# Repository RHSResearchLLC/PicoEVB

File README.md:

# PicoEVB: M.2/NGFF based Xilinx Artix-7 development board

PicoEVB is an affordable development board which can be used to evaluate and prototype 
PCI express designs using Xilinx Artix 7 FPGA on Windows or Linux hosts.
The board is designed around the Artix 7 (XC7A50T).

PicoEVB is a complete development system in a M.2 (NGFF) 2230 footprint. The JTAG cable
and all necessary power supplies are built in. It will work in the following slots:
 
- M.2 2230 Key A
- M.2 2230 Key E
- M.2 2280 Key M via an adapter [like this one](https://www.amazon.com/gp/product/B079NB8J3B)
- Full length mini PCIe via an adapter [like this one](https://www.amazon.com/dp/B01MR76H5F)
- PCIe x1, x4, x8, or x16 slot via an adapter [like this one](https://www.amazon.com/dp/B013U4401W) 

## Features
- PCI Express connection to the host via M.2 edge slot
- Built-in JTAG cable works with Vivado and Labtools
- Analog and digital IO

## Specifications

| Feature | Specification |
| --- | --- |
| FPGA | Xilinx Artix XC7A50T-2CSG325C |
| Form Factor | M.2 (NGFF), keyed for A and E slots |
| Dimensions | 22x30x3.8 mm |
| Host Interface | PCIe x1 gen 2 (5 Gb/s) |
| Host Tools | Vivado 2017.3 preferred |
| MGT Loopback | Yes |
| Built-in JTAG | Yes |
| External I/O configurations <BR/> via I/O connector | (digital+ differential analog) <BR/> 4+0 <BR/> 2+1 <BR/> 0+2 |
| External I/O via PCIe connector | 4x 3.3V digital I/O (configurable) |
| External MGT connection | 1x MGT via U.FL connectors |
| External clock ref | 1x clkin via U.FL connectors |
| User-controllable LEDs | 3 |

## Block Diagram

## How to get one

- [Product Website](https://www.picoevb.com)
- [Amazon](https://www.amazon.com/dp/B0779PC8S4)
- [Crowd Supply](https://www.crowdsupply.com/rhs-research/nanoevb)
- [EBay](https://www.ebay.com/itm/232775706324)

## More information

- [Check out the wiki](https://github.com/RHSResearchLLC/NanoEVB-X1/wiki)
- [Product Website](https://www.picoevb.com)

or contact info@nanoevb.com

** Note: This page applies to PicoEVB Rev D. For previous revs, select the rev from tags **

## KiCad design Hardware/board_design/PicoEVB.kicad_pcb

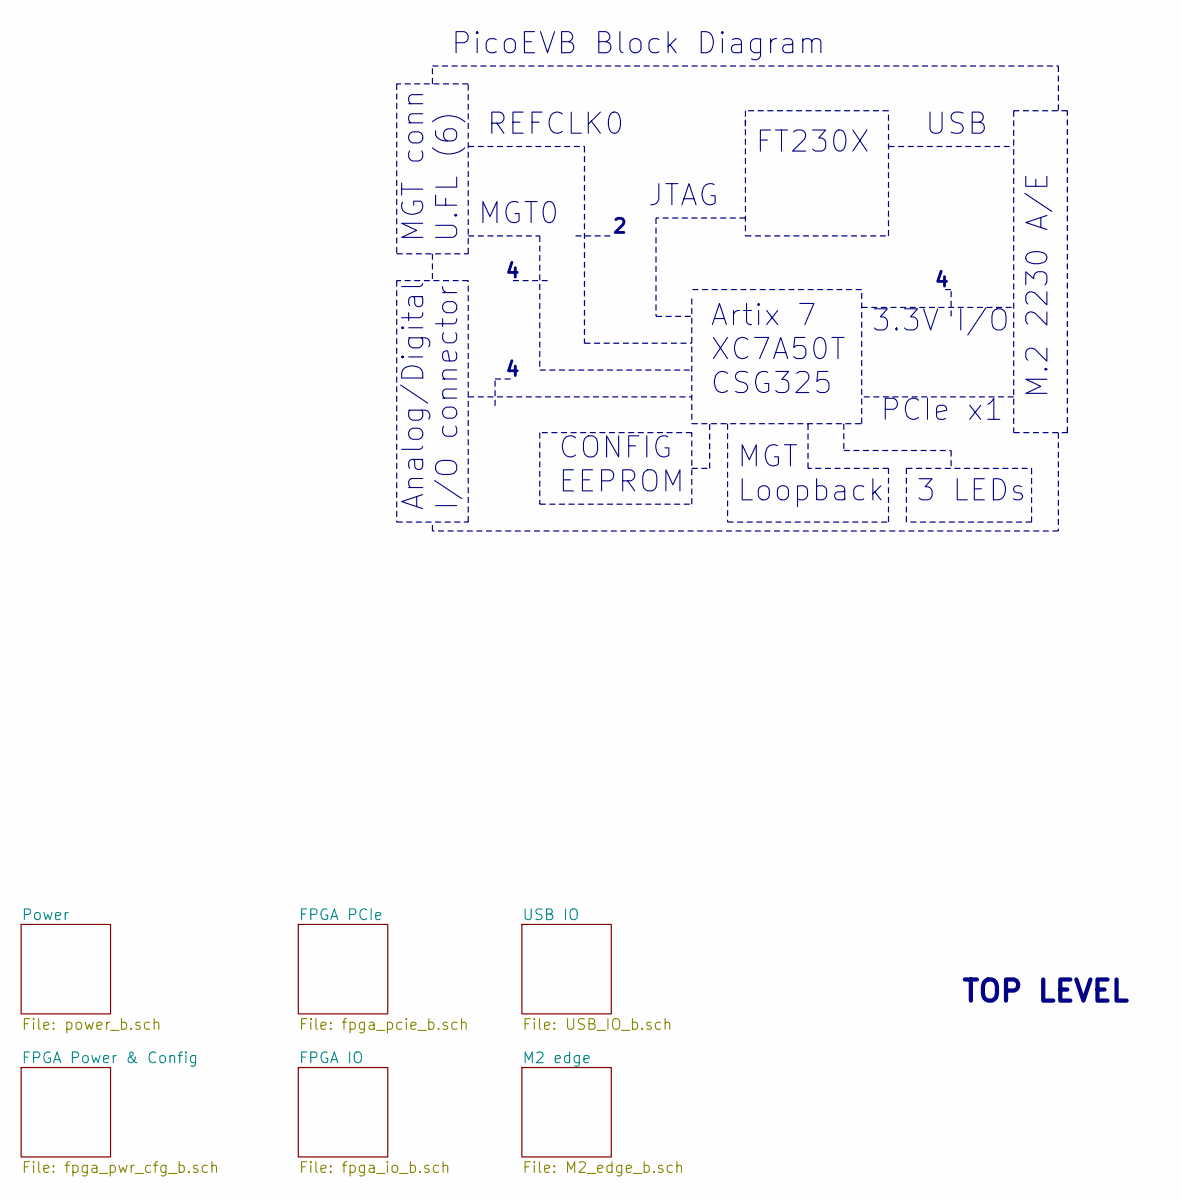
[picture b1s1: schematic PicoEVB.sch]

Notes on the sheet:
TOP LEVEL
M.2 2230 A/E
FT230X
USB
Artix 7 XC7A50T CSG325
PCIe x1
JTAG
MGT Loopback
Analog/Digital I/O connector
PicoEVB Block Diagram
3 LEDs
CONFIG EEPROM
MGT conn U.FL (6)
MGT0
REFCLK0
3.3V I/O

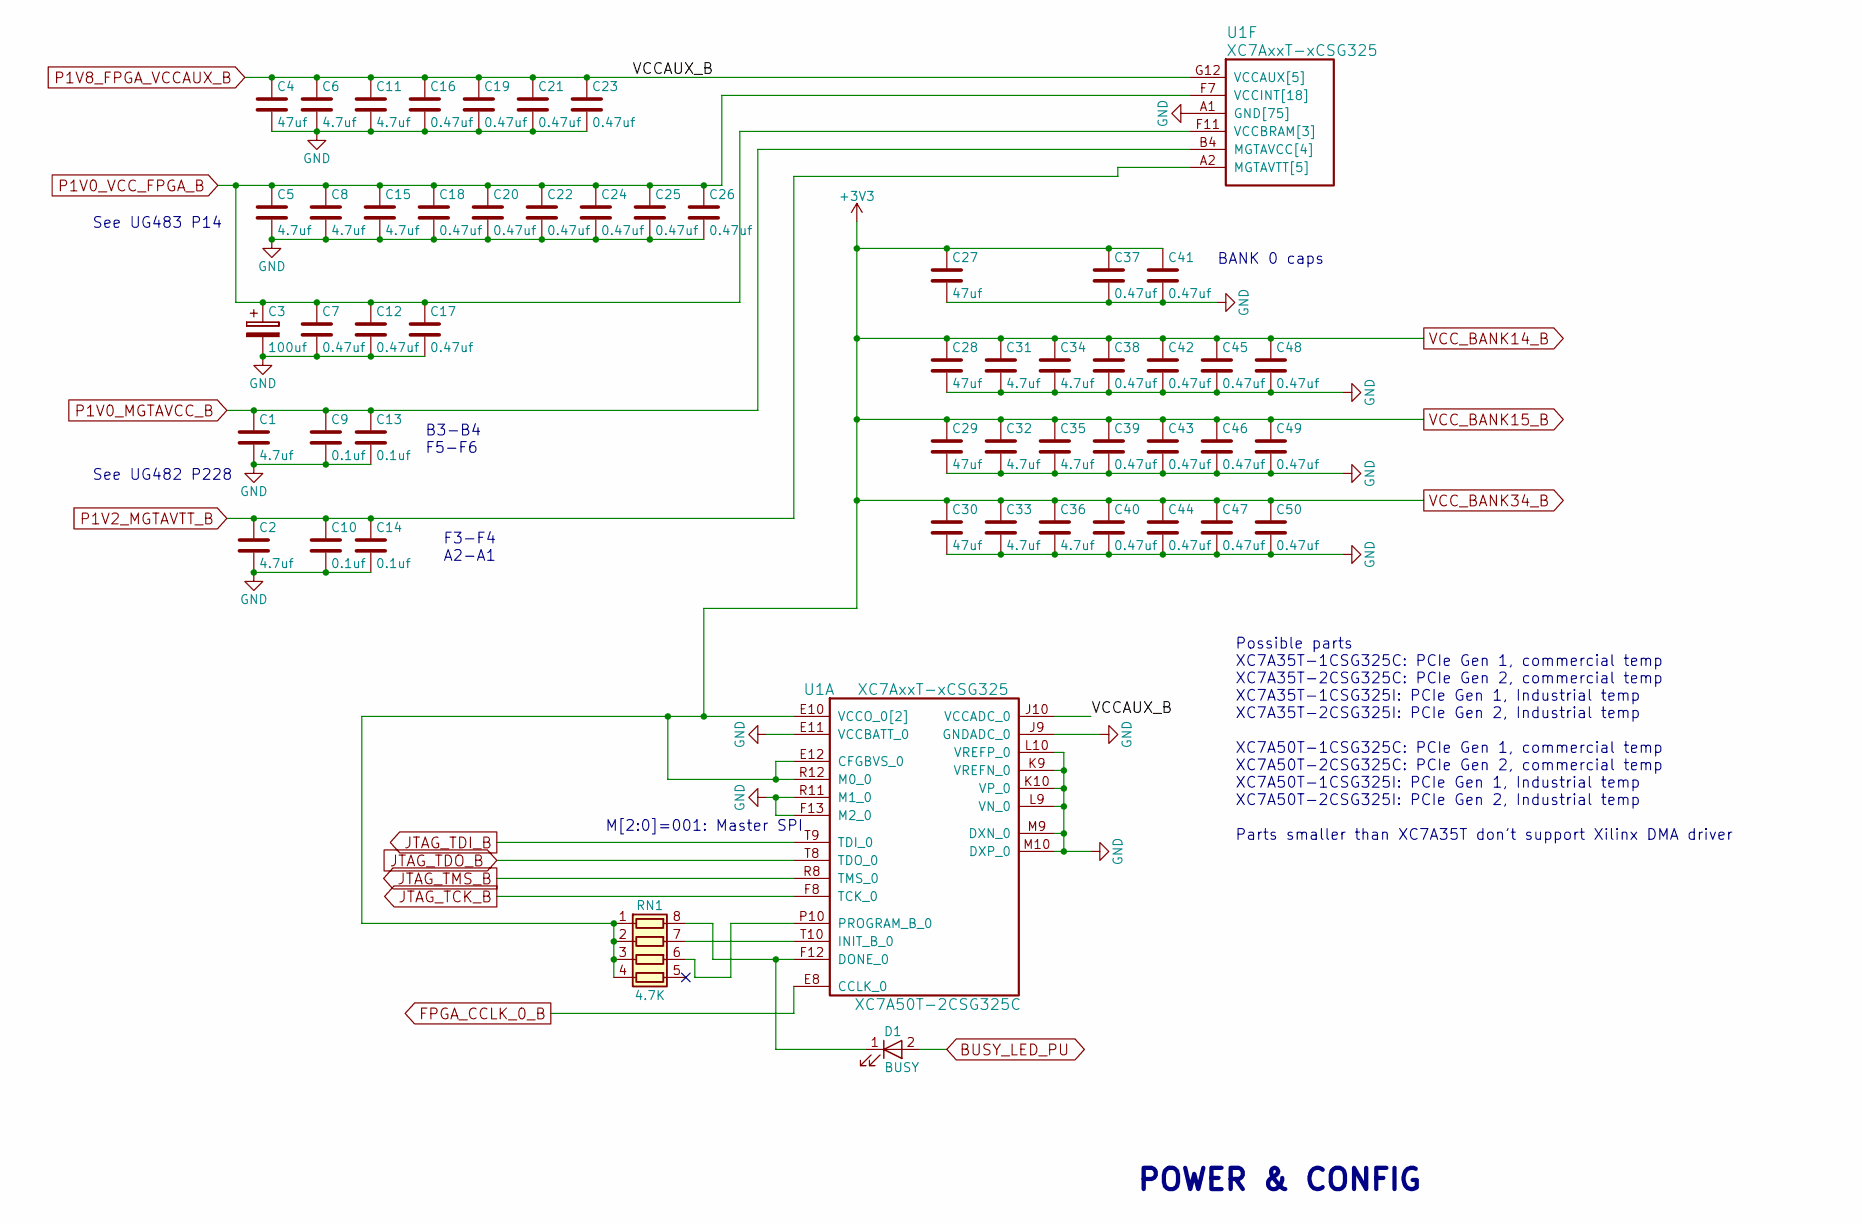
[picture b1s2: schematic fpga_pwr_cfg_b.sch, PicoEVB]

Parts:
C1, C2, C5, C6, C8, C11, C15, C31, C32, C33, C34, C35, C36: 4.7uf; c_0402; MPN CC0402MRX5R5BB475
C3: 100uf; C_0805; MPN F950J107MPAAQ2
C4, C27, C28, C29, C30: 47uf; C_0603; MPN GRM188R60G476ME15D
C7, C12, C16, C17, C18, C19, C20, C21, C22, C23, C24, C25, C26, C37, C38, C39, C40, C41, C42, C43, C44, C45, C46, C47, C48, C49, C50: 0.47uf; c_0201_least; MPN cc0201krx5r5bb474
C9, C10, C13, C14: 0.1uf; c_0201_least; MPN cc0201krx5r5bb104
D1: BUSY; LED_0402; MPN LNJ247W82RA
RN1: 4.7K; R_Array_Convex_4x0402; MPN 741X083472JP
U1: XC7AxxT-xCSG325

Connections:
BUSY_LED_PU: D1.2 (A); also elsewhere on the board
FPGA_CCLK_0_B: U1.E8 (CCLK_0); also elsewhere on the board
GND: C1.2, C2.2, C3.2, C4.2, C5.2, C6.2, C7.2, C8.2, C9.2, C10.2, C11.2, C12.2, C13.2, C14.2, C15.2, C16.2, C17.2, C18.2, C19.2, C20.2, C21.2, C22.2, C23.2, C24.2, C25.2, C26.2, C27.2, C28.2, C29.2, C30.2, C31.2, C32.2, C33.2, C34.2, C35.2, C36.2, C37.2, C38.2, C39.2, C40.2, C41.2, C42.2, C43.2, C44.2, C45.2, C46.2, C47.2, C48.2, C49.2, C50.2, U1.A1 (GND[75]), U1.A5 (GND[75]), U1.A7 (GND[75]), U1.A8 (GND[75]), U1.A11 (GND[75]), U1.A18 (GND[75]), U1.B3 (GND[75]), U1.B7 (GND[75]), U1.B8 (GND[75]), U1.B18 (GND[75]), U1.C2 (GND[75]), U1.C6 (GND[75]), U1.C7 (GND[75]), U1.C15 (GND[75]), U1.D3 (GND[75]), U1.D4 (GND[75]), U1.D7 (GND[75]), U1.D12 (GND[75]), U1.E2 (GND[75]), U1.E6 (GND[75]), U1.E7 (GND[75]), U1.E9 (GND[75]), U1.E11 (VCCBATT_0), U1.F4 (GND[75]), U1.F6 (GND[75]), U1.F10 (GND[75]), U1.F13 (M2_0), U1.F16 (GND[75]), U1.G1 (GND[75]), U1.G5 (GND[75]), U1.G6 (GND[75]), U1.G7 (GND[75]), U1.G9 (GND[75]), U1.G11 (GND[75]), U1.G13 (GND[75]), U1.H3 (GND[75]), U1.H4 (GND[75]), U1.H5 (GND[75]), U1.H6 (GND[75]), U1.H8 (GND[75]), U1.H10 (GND[75]), U1.H12 (GND[75]), U1.J1 (GND[75]), U1.J2 (GND[75]), U1.J3 (GND[75]), U1.J7 (GND[75]), U1.J9 (GNDADC_0), U1.J11 (GND[75]), U1.J13 (GND[75]), U1.J17 (GND[75]), U1.K4 (GND[75]), U1.K8 (GND[75]), U1.K9 (VREFN_0), U1.K10 (VP_0), U1.K12 (GND[75]), U1.K14 (GND[75]), U1.L1 (GND[75]), U1.L7 (GND[75]), U1.L9 (VN_0), U1.L10 (VREFP_0), U1.L11 (GND[75]), U1.L13 (GND[75]), U1.M8 (GND[75]), U1.M9 (DXN_0), U1.M10 (DXP_0), U1.M12 (GND[75]), U1.M18 (GND[75]), U1.N5 (GND[75]), U1.N7 (GND[75]), U1.N9 (GND[75]), U1.N11 (GND[75]), U1.N13 (GND[75]), U1.N15 (GND[75]), U1.P2 (GND[75]), U1.P8 (GND[75]), U1.P12 (GND[75]), U1.R9 (GND[75]), U1.R11 (M1_0), U1.T6 (GND[75]), U1.T16 (GND[75]), U1.U3 (GND[75]), U1.U13 (GND[75]), U1.V1 (GND[75]), U1.V10 (GND[75]), U1.V18 (GND[75]); also elsewhere on the board
JTAG_TCK_B: U1.F8 (TCK_0); also elsewhere on the board
JTAG_TDI_B: U1.T9 (TDI_0); also elsewhere on the board
JTAG_TDO_B: U1.T8 (TDO_0); also elsewhere on the board
JTAG_TMS_B: U1.R8 (TMS_0); also elsewhere on the board
unnamed: D1.1 (K), RN1.8 (R1.2), U1.F12 (DONE_0)
unnamed: RN1.6 (R3.2), U1.P10 (PROGRAM_B_0)
unnamed: RN1.7 (R2.2), U1.T10 (INIT_B_0)
P1V0_MGTAVCC_B: C1.1, C9.1, C13.1, U1.B4 (MGTAVCC[4]), U1.C5 (MGTAVCC[4]), U1.E5 (MGTAVCC[4]), U1.F5 (MGTAVCC[4]); also elsewhere on the board
P1V0_VCC_FPGA_B: C3.1, C5.1, C7.1, C8.1, C12.1, C15.1, C17.1, C18.1, C20.1, C22.1, C24.1, C25.1, C26.1, U1.F7 (VCCINT[18]), U1.F9 (VCCINT[18]), U1.F11 (VCCBRAM[3]), U1.G8 (VCCINT[18]), U1.G10 (VCCBRAM[3]), U1.H7 (VCCINT[18]), U1.H9 (VCCINT[18]), U1.H11 (VCCBRAM[3]), U1.J8 (VCCINT[18]), U1.J12 (VCCINT[18]), U1.K7 (VCCINT[18]), U1.K11 (VCCINT[18]), U1.L8 (VCCINT[18]), U1.L12 (VCCINT[18]), U1.M7 (VCCINT[18]), U1.M11 (VCCINT[18]), U1.N8 (VCCINT[18]), U1.N10 (VCCINT[18]), U1.N12 (VCCINT[18]), U1.P9 (VCCINT[18]), U1.P11 (VCCINT[18]); also elsewhere on the board
P1V2_MGTAVTT_B: C2.1, C10.1, C14.1, U1.A2 (MGTAVTT[5]), U1.C1 (MGTAVTT[5]), U1.E1 (MGTAVTT[5]), U1.F3 (MGTAVTT[5]), U1.G2 (MGTAVTT[5]); also elsewhere on the board
P1V8_FPGA_VCCAUX_B: C4.1, C6.1, C11.1, C16.1, C19.1, C21.1, C23.1, U1.G12 (VCCAUX[5]), U1.H13 (VCCAUX[5]), U1.J10 (VCCADC_0), U1.K13 (VCCAUX[5]), U1.M13 (VCCAUX[5]), U1.P13 (VCCAUX[5]); also elsewhere on the board
VCC_BANK14_B: C27.1, C28.1, C29.1, C30.1, C31.1, C32.1, C33.1, C34.1, C35.1, C36.1, C37.1, C38.1, C39.1, C40.1, C41.1, C42.1, C43.1, C44.1, C45.1, C46.1, C47.1, C48.1, C49.1, C50.1, RN1.1 (R1.1), RN1.2 (R2.1), RN1.3 (R3.1), RN1.4 (R4.1), U1.E10 (VCCO_0[2]), U1.E12 (CFGBVS_0), U1.R10 (VCCO_0[2]), U1.R12 (M0_0); also elsewhere on the board

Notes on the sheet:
See UG482 P228
See UG483 P14
M[2:0]=001: Master SPI
B3-B4 F5-F6
F3-F4 A2-A1
POWER & CONFIG
BANK 0 caps
Possible parts XC7A35T-1CSG325C: PCIe Gen 1, commercial temp XC7A35T-2CSG325C: PCIe Gen 2, commercial temp XC7A35T-1CSG325I: PCIe Gen 1, Industrial temp XC7A35T-2CSG325I: PCIe Gen 2, Industrial temp XC7A50T-1CSG325C: PCIe Gen 1, commercial temp XC7A50T-2CSG325C: PCIe Gen 2, commercial temp XC7A50T-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

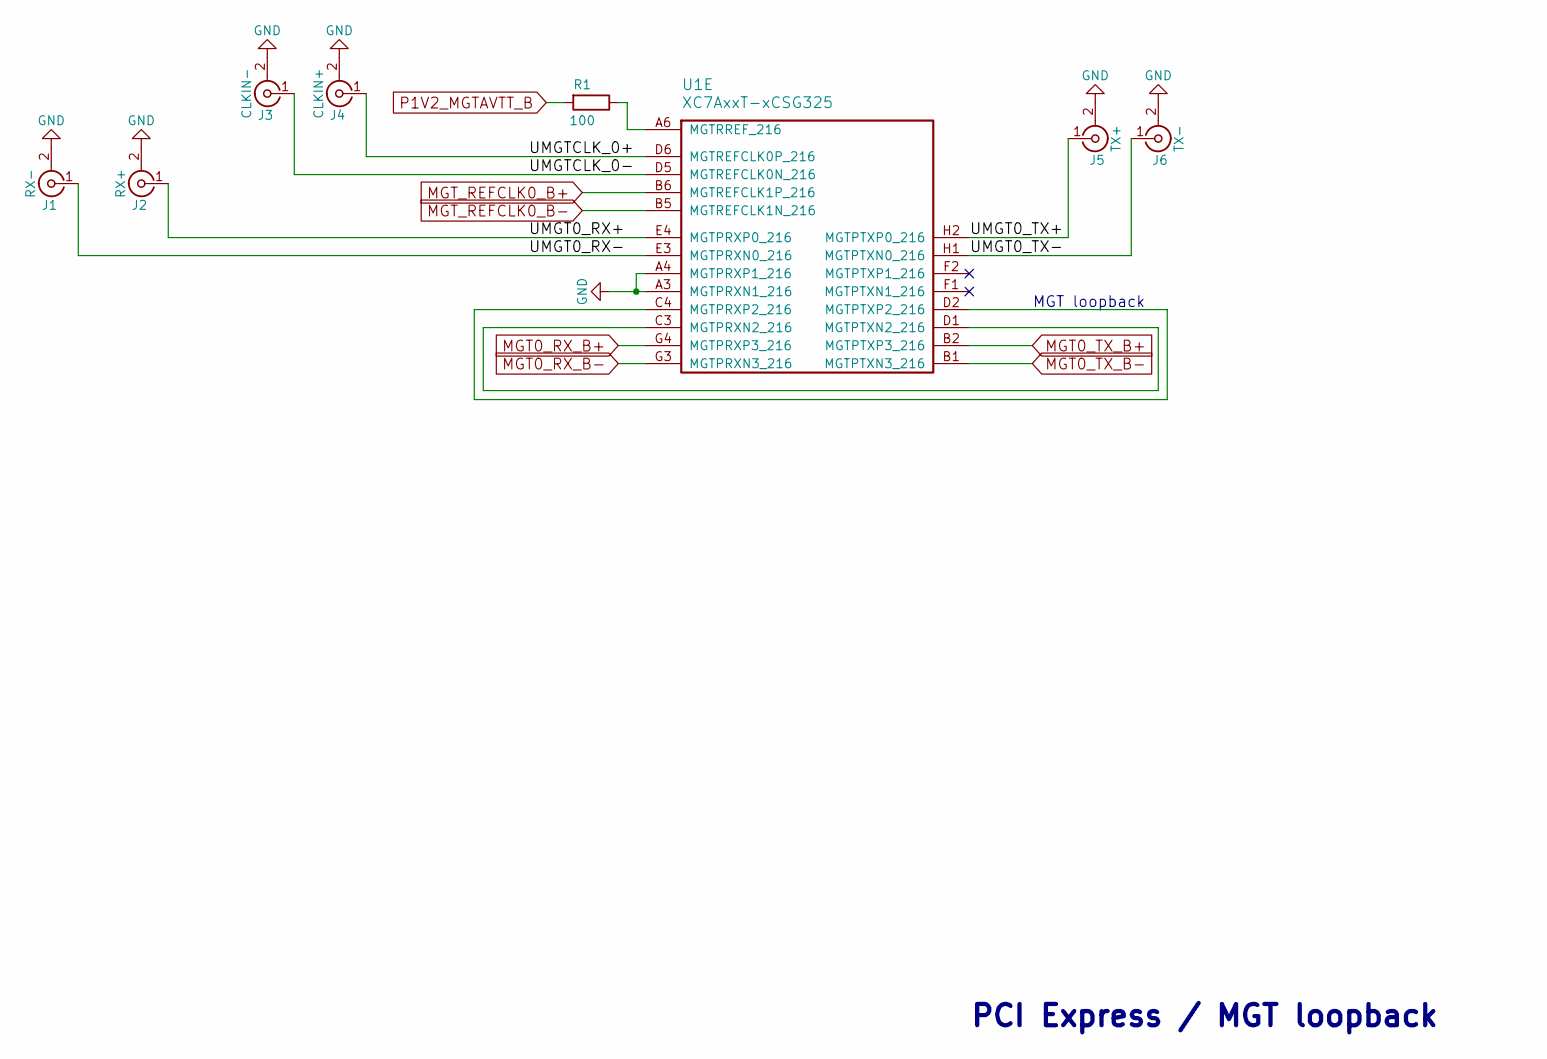
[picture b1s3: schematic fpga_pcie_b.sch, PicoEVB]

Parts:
J1: RX-; U.FL-COAX; MPN U.FL-R-SMT(10)
J2: RX+; U.FL-COAX; MPN U.FL-R-SMT(10)
J3: CLKIN-; U.FL-COAX; MPN U.FL-R-SMT(10)
J4: CLKIN+; U.FL-COAX; MPN U.FL-R-SMT(10)
J5: TX+; U.FL-COAX; MPN U.FL-R-SMT(10)
J6: TX-; U.FL-COAX; MPN U.FL-R-SMT(10)
R1: 100; r_0201_least; MPN RC0201FR-07100RL
U1: XC7AxxT-xCSG325

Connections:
/FPGA PCIe/UMGT0_RX+: J2.1 (In), U1.E4 (MGTPRXP0_216)
/FPGA PCIe/UMGT0_RX-: J1.1 (In), U1.E3 (MGTPRXN0_216)
/FPGA PCIe/UMGT0_TX+: J5.1 (In), U1.H2 (MGTPTXP0_216)
/FPGA PCIe/UMGT0_TX-: J6.1 (In), U1.H1 (MGTPTXN0_216)
/FPGA PCIe/UMGTCLK_0+: J4.1 (In), U1.D6 (MGTREFCLK0P_216)
/FPGA PCIe/UMGTCLK_0-: J3.1 (In), U1.D5 (MGTREFCLK0N_216)
GND: J1.2 (Ext), J2.2 (Ext), J3.2 (Ext), J4.2 (Ext), J5.2 (Ext), J6.2 (Ext), U1.A3 (MGTPRXN1_216), U1.A4 (MGTPRXP1_216); also elsewhere on the board
MGT0_RX_B+: U1.G4 (MGTPRXP3_216); also elsewhere on the board
MGT0_RX_B-: U1.G3 (MGTPRXN3_216); also elsewhere on the board
MGT0_TX_B+: U1.B2 (MGTPTXP3_216); also elsewhere on the board
MGT0_TX_B-: U1.B1 (MGTPTXN3_216); also elsewhere on the board
MGT_REFCLK0_B+: U1.B6 (MGTREFCLK1P_216); also elsewhere on the board
MGT_REFCLK0_B-: U1.B5 (MGTREFCLK1N_216); also elsewhere on the board
unnamed: R1.1, U1.A6 (MGTRREF_216)
unnamed: U1.C3 (MGTPRXN2_216), U1.D1 (MGTPTXN2_216)
unnamed: U1.C4 (MGTPRXP2_216), U1.D2 (MGTPTXP2_216)
P1V2_MGTAVTT_B: R1.2; also elsewhere on the board

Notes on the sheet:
MGT loopback
PCI Express / MGT loopback

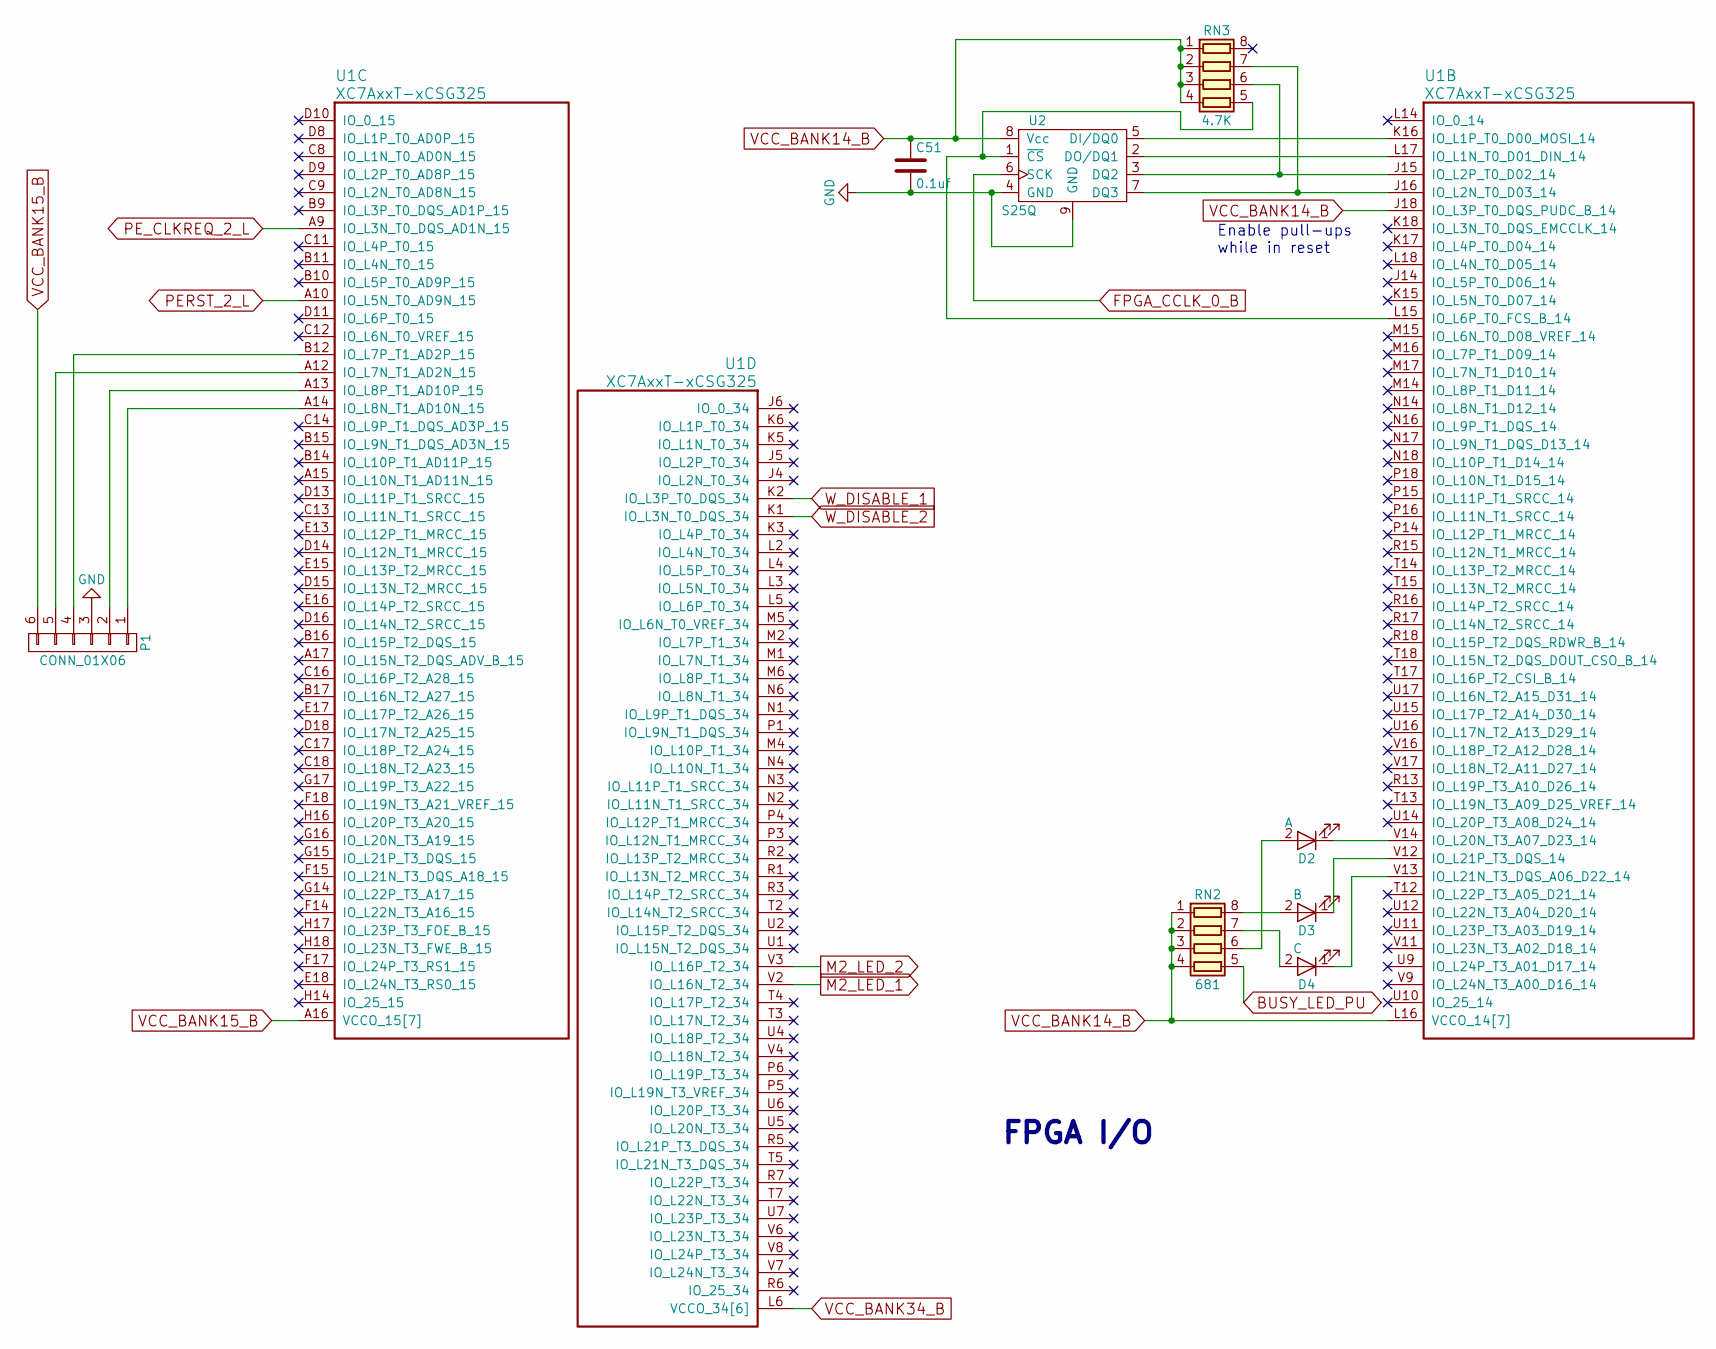
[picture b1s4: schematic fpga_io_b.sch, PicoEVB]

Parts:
C51: 0.1uf; c_0201_least; MPN cc0201krx5r5bb104
D2: A; LED_0402; MPN LNJ247W82RA
D3: B; LED_0402; MPN LNJ247W82RA
D4: C; LED_0402; MPN LNJ247W82RA
P1: CONN_01X06; pico-ezmate-6; MPN 78171-5006
RN2: 681; R_Array_Convex_4x0402; MPN 741X083681JP
RN3: 4.7K; R_Array_Convex_4x0402; MPN 741X083472JP
U1: XC7AxxT-xCSG325
U2: S25Q; SOIC-8_3.9x4.9mm_Pitch1.27mm; MPN S25FL032P0XNFI011

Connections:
BUSY_LED_PU: RN2.5 (R4.2); also elsewhere on the board
FPGA_CCLK_0_B: U2.6 (SCK); also elsewhere on the board
GND: C51.2, P1.3, U2.4 (GND), U2.9 (GND); also elsewhere on the board
M2_LED_1: U1.V2 (IO_L16N_T2_34); also elsewhere on the board
M2_LED_2: U1.V3 (IO_L16P_T2_34); also elsewhere on the board
unnamed: D2.1 (K), U1.V14 (IO_L20N_T3_A07_D23_14)
unnamed: D2.2 (A), RN2.6 (R3.2)
unnamed: D3.1 (K), U1.V12 (IO_L21P_T3_DQS_14)
unnamed: D3.2 (A), RN2.8 (R1.2)
unnamed: D4.1 (K), U1.V13 (IO_L21N_T3_DQS_A06_D22_14)
unnamed: D4.2 (A), RN2.7 (R2.2)
unnamed: P1.1, U1.A14 (IO_L8N_T1_AD10N_15)
unnamed: P1.2, U1.A13 (IO_L8P_T1_AD10P_15)
unnamed: P1.4, U1.B12 (IO_L7P_T1_AD2P_15)
unnamed: P1.5, U1.A12 (IO_L7N_T1_AD2N_15)
unnamed: RN3.5 (R4.2), U1.L15 (IO_L6P_T0_FCS_B_14), U2.1 (~CS)
unnamed: RN3.6 (R3.2), U1.J15 (IO_L2P_T0_D02_14), U2.3 (DQ2)
unnamed: RN3.7 (R2.2), U1.J16 (IO_L2N_T0_D03_14), U2.7 (DQ3)
unnamed: U1.K16 (IO_L1P_T0_D00_MOSI_14), U2.5 (DI/DQ0)
unnamed: U1.L17 (IO_L1N_T0_D01_DIN_14), U2.2 (DO/DQ1)
PERST_2_L: U1.A10 (IO_L5N_T0_AD9N_15); also elsewhere on the board
PE_CLKREQ_2_L: U1.A9 (IO_L3N_T0_DQS_AD1N_15); also elsewhere on the board
VCC_BANK14_B: C51.1, P1.6, RN2.1 (R1.1), RN2.2 (R2.1), RN2.3 (R3.1), RN2.4 (R4.1), RN3.1 (R1.1), RN3.2 (R2.1), RN3.3 (R3.1), RN3.4 (R4.1), U1.A16 (VCCO_15[7]), U1.B13 (VCCO_15[7]), U1.C10 (VCCO_15[7]), U1.D17 (VCCO_15[7]), U1.E14 (VCCO_15[7]), U1.G18 (VCCO_15[7]), U1.H15 (VCCO_15[7]), U1.J18 (IO_L3P_T0_DQS_PUDC_B_14), U1.L6 (VCCO_34[6]), U1.L16 (VCCO_14[7]), U1.M3 (VCCO_34[6]), U1.P7 (VCCO_34[6]), U1.P17 (VCCO_14[7]), U1.R4 (VCCO_34[6]), U1.R14 (VCCO_14[7]), U1.T1 (VCCO_34[6]), U1.T11 (VCCO_14[7]), U1.U8 (VCCO_14[7]), U1.U18 (VCCO_14[7]), U1.V5 (VCCO_34[6]), U1.V15 (VCCO_14[7]), U2.8 (Vcc); also elsewhere on the board
W_DISABLE_1: U1.K2 (IO_L3P_T0_DQS_34); also elsewhere on the board
W_DISABLE_2: U1.K1 (IO_L3N_T0_DQS_34); also elsewhere on the board

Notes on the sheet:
Enable pull-ups while in reset
FPGA I/O

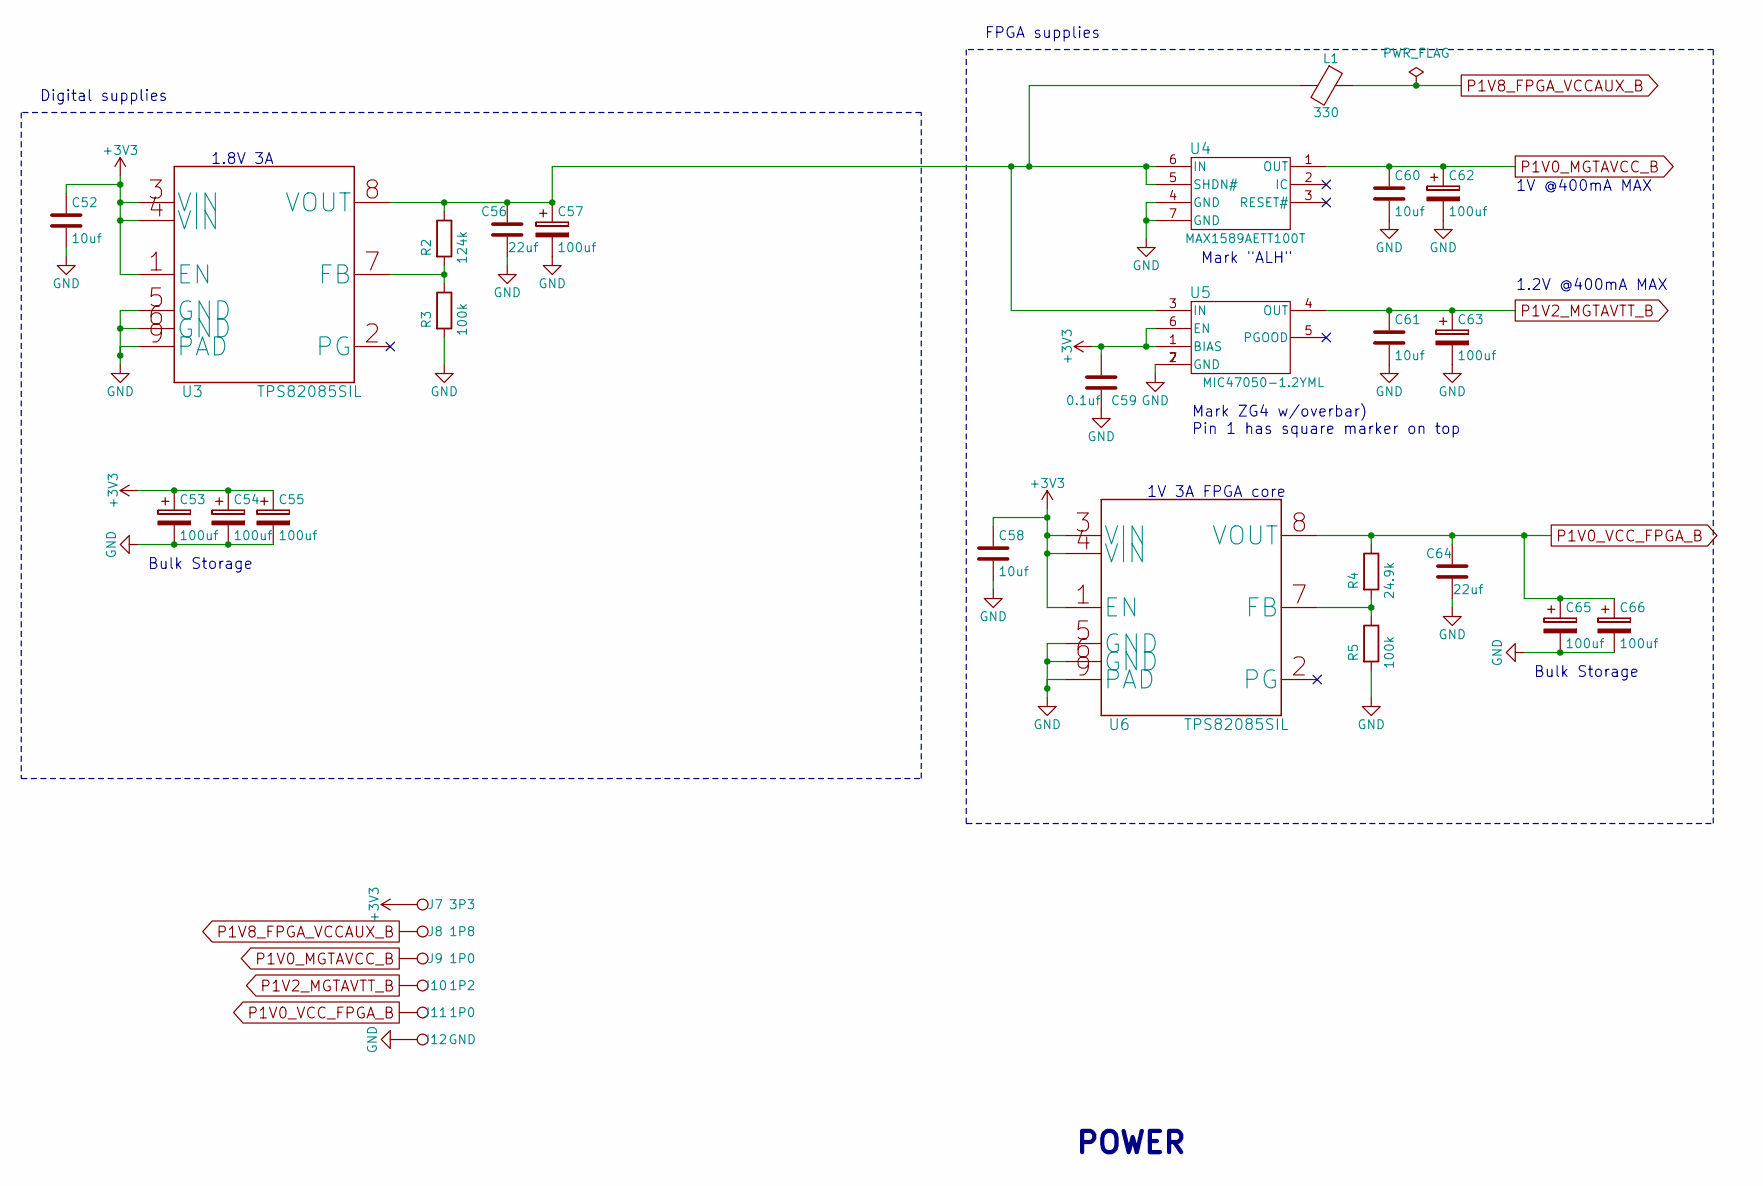
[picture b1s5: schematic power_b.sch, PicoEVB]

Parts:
C52, C58, C60, C61: 10uf; c_0402; MPN CC0402MRX5R5BB106
C53, C54, C55, C57, C62, C63, C65, C66: 100uf; C_0805; MPN F950J107MPAAQ2
C56, C64: 22uf; C_0603; MPN CC0603MRX5R6BB226
C59: 0.1uf; c_0201_least; MPN cc0201krx5r5bb104
J7: 3P3; SolderWirePad_single_SMD_1x1mm
J8: 1P8; SolderWirePad_single_SMD_1x1mm
J9, J11: 1P0; SolderWirePad_single_SMD_1x1mm
J10: 1P2; SolderWirePad_single_SMD_1x1mm
J12: GND; SolderWirePad_single_SMD_1x1mm
L1: 330; r_0402; MPN BKP1005EM331-T
R2: 124k; r_0201_least; MPN RC0201FR-07124KL
R3, R5: 100k; r_0201_least; MPN RC0201FR-07100KL
R4: 24.9k; r_0201_least; MPN RC0201FR-0724K9L
U3, U6: TPS82085SIL; TPS82084SILR; MPN TPS82085SILT
U4: MAX1589AETT100T; MPN MAX1589AETT100+T
U5: MIC47050-1.2YML; MIC47050-DFN-6-2MM; MPN MIC47050-1.2YML-TR

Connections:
GND: C52.2, C53.2, C54.2, C55.2, C56.2, C57.2, C58.2, C59.2, C60.2, C61.2, C62.2, C63.2, C64.2, C65.2, C66.2, J12.1, R3.2, R5.2, U3.5 (GND), U3.6 (GND), U3.9 (PAD), U4.4 (GND), U4.7 (GND), U5.2 (GND), U5.7 (GND), U6.5 (GND), U6.6 (GND), U6.9 (PAD); also elsewhere on the board
unnamed: C56.1, C57.1, L1.2, R2.1, U3.8 (VOUT), U4.5 (SHDN#), U4.6 (IN), U5.3 (IN)
unnamed: R2.2, R3.1, U3.7 (FB)
unnamed: R4.2, R5.1, U6.7 (FB)
P1V0_MGTAVCC_B: C60.1, C62.1, J9.1, U4.1 (OUT); also elsewhere on the board
P1V0_VCC_FPGA_B: C64.1, C65.1, C66.1, J11.1, R4.1, U6.8 (VOUT); also elsewhere on the board
P1V2_MGTAVTT_B: C61.1, C63.1, J10.1, U5.4 (OUT); also elsewhere on the board
P1V8_FPGA_VCCAUX_B: J8.1, L1.1; also elsewhere on the board
VCC_BANK14_B: C52.1, C53.1, C54.1, C55.1, C58.1, C59.1, J7.1, U3.1 (EN), U3.3 (VIN), U3.4 (VIN), U5.1 (BIAS), U5.6 (EN), U6.1 (EN), U6.3 (VIN), U6.4 (VIN); also elsewhere on the board

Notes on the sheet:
1.8V 3A
1V 3A FPGA core
1V @400mA MAX
1.2V @400mA MAX
Digital supplies
FPGA supplies
Bulk Storage
Mark "ALH"
Mark ZG4 w/overbar) Pin 1 has square marker on top
POWER

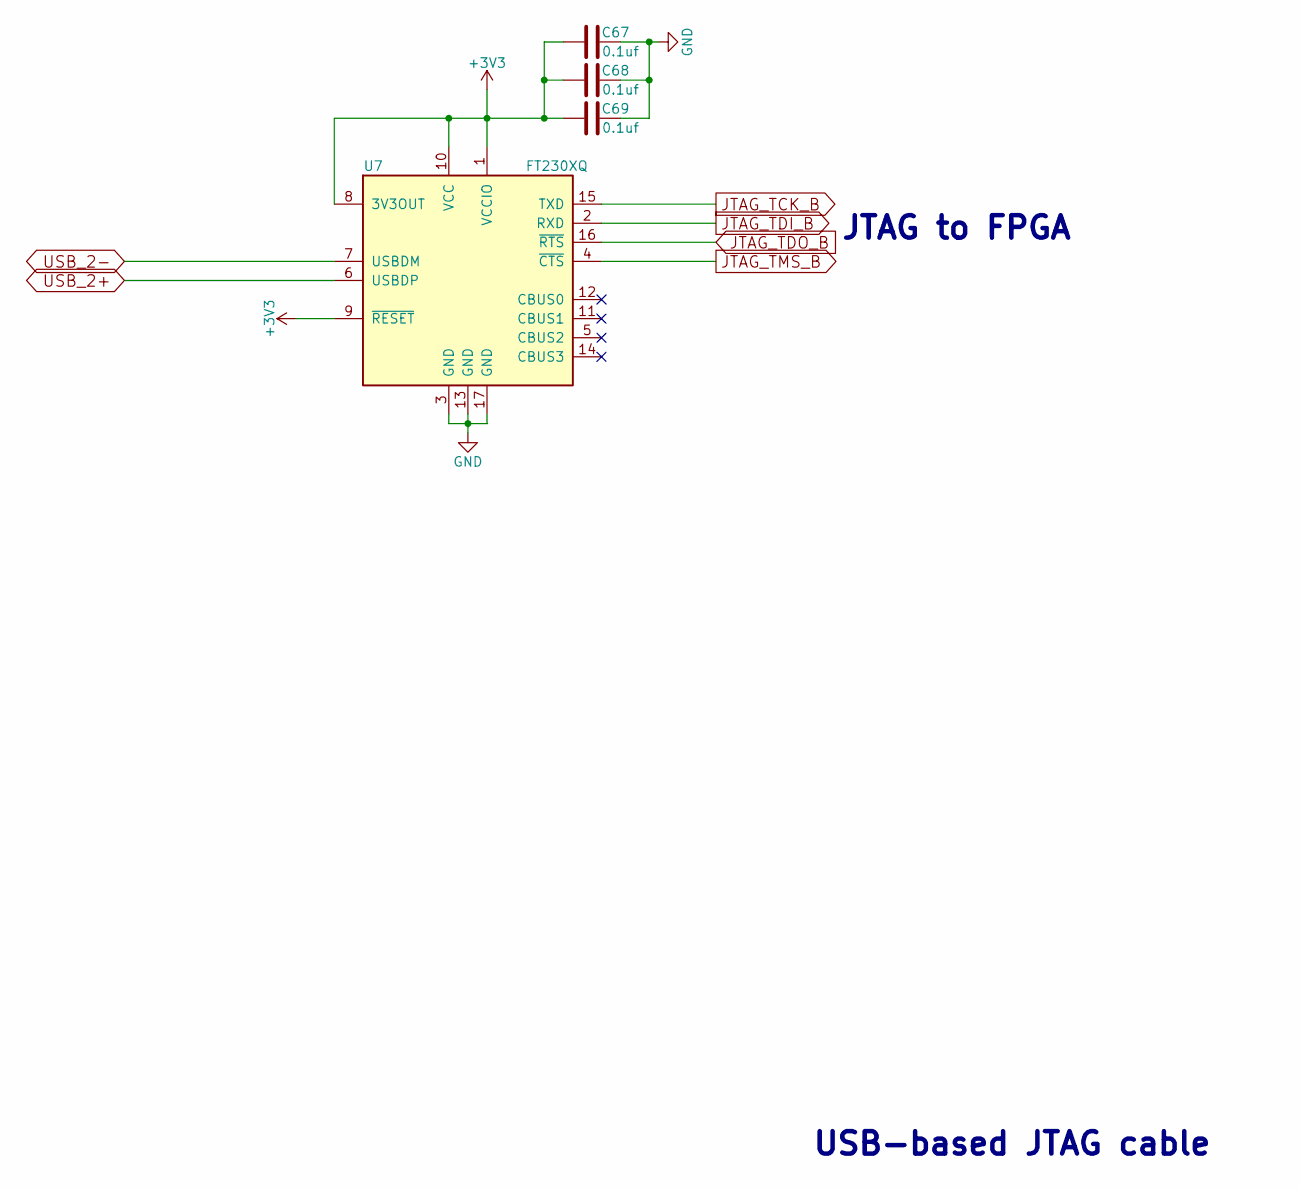
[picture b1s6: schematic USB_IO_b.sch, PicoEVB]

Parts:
C67, C68, C69: 0.1uf; c_0201_least; MPN cc0201krx5r5bb104
U7: FT230XQ; QFN-16-1EP_4x4mm_Pitch0.65mm; MPN FT230XQ

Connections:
GND: C67.2, C68.2, C69.2, U7.3 (GND), U7.13 (GND), U7.17 (GND); also elsewhere on the board
JTAG_TCK_B: U7.15 (TXD); also elsewhere on the board
JTAG_TDI_B: U7.2 (RXD); also elsewhere on the board
JTAG_TDO_B: U7.16 (~RTS); also elsewhere on the board
JTAG_TMS_B: U7.4 (~CTS); also elsewhere on the board
USB_2+: U7.6 (USBDP); also elsewhere on the board
USB_2-: U7.7 (USBDM); also elsewhere on the board
VCC_BANK14_B: C67.1, C68.1, C69.1, U7.1 (VCCIO), U7.8 (3V3OUT), U7.9 (~RESET), U7.10 (VCC); also elsewhere on the board

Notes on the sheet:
USB-based JTAG cable
JTAG to FPGA

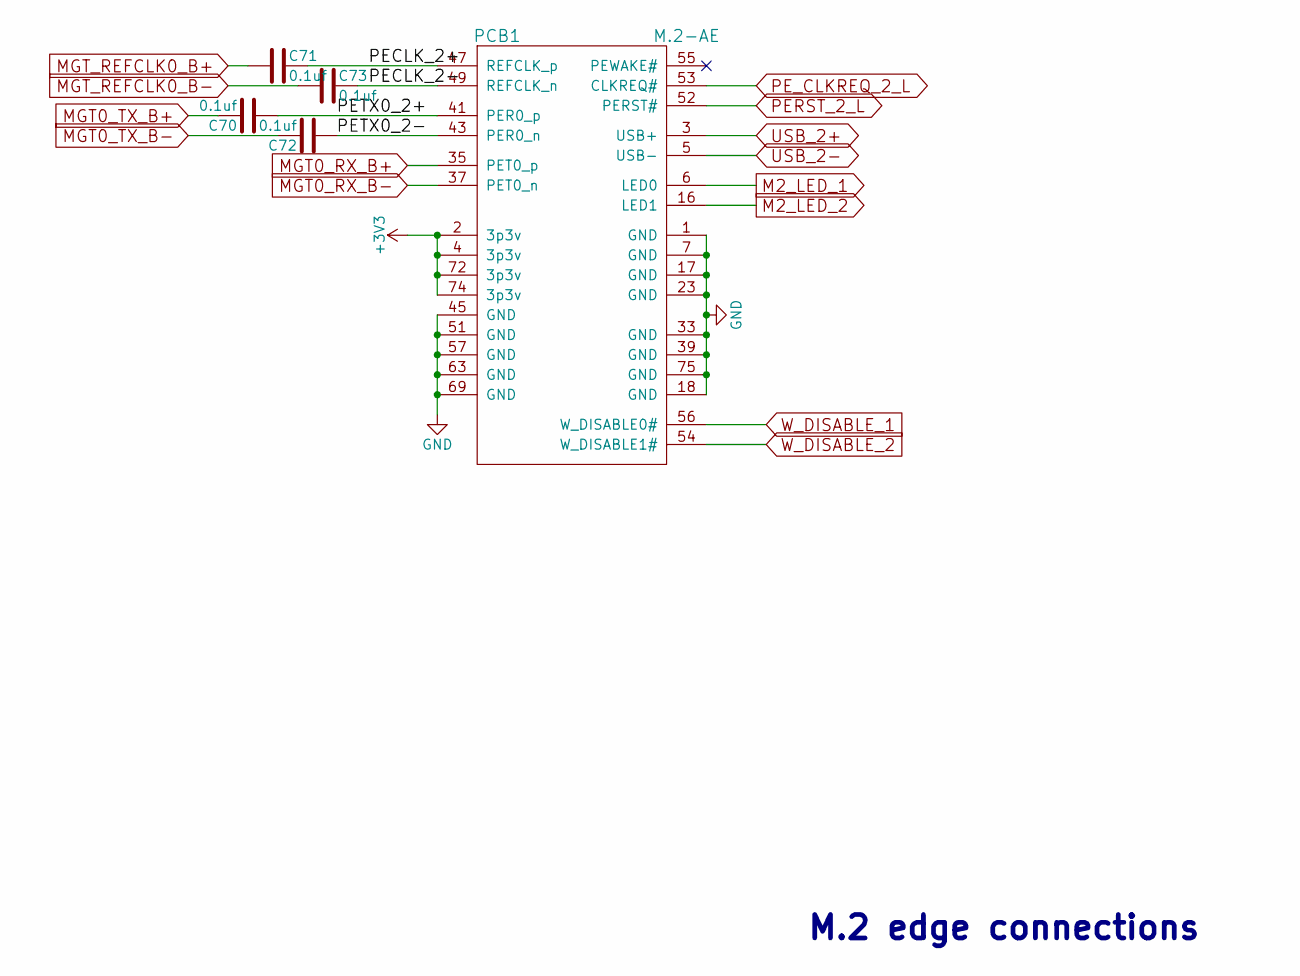
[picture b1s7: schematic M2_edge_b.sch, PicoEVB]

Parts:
C70, C71, C72, C73: 0.1uf; c_0201_least; MPN cc0201krx5r5bb104
PCB1: M.2-AE; M.2-AE-22x42; MPN xxx

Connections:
/M2 edge/PECLK_2+: C71.1, PCB1.47 (REFCLK_p)
/M2 edge/PECLK_2-: C73.1, PCB1.49 (REFCLK_n)
/M2 edge/PETX0_2+: C70.2, PCB1.41 (PER0_p)
/M2 edge/PETX0_2-: C72.2, PCB1.43 (PER0_n)
GND: PCB1.1 (GND), PCB1.7 (GND), PCB1.17 (GND), PCB1.18 (GND), PCB1.23 (GND), PCB1.33 (GND), PCB1.39 (GND), PCB1.45 (GND), PCB1.51 (GND), PCB1.57 (GND), PCB1.63 (GND), PCB1.69 (GND), PCB1.75 (GND); also elsewhere on the board
M2_LED_1: PCB1.6 (LED0); also elsewhere on the board
M2_LED_2: PCB1.16 (LED1); also elsewhere on the board
MGT0_RX_B+: PCB1.35 (PET0_p); also elsewhere on the board
MGT0_RX_B-: PCB1.37 (PET0_n); also elsewhere on the board
MGT0_TX_B+: C70.1; also elsewhere on the board
MGT0_TX_B-: C72.1; also elsewhere on the board
MGT_REFCLK0_B+: C71.2; also elsewhere on the board
MGT_REFCLK0_B-: C73.2; also elsewhere on the board
PERST_2_L: PCB1.52 (PERST#); also elsewhere on the board
PE_CLKREQ_2_L: PCB1.53 (CLKREQ#); also elsewhere on the board
USB_2+: PCB1.3 (USB+); also elsewhere on the board
USB_2-: PCB1.5 (USB-); also elsewhere on the board
VCC_BANK14_B: PCB1.2 (3p3v), PCB1.4 (3p3v), PCB1.72 (3p3v), PCB1.74 (3p3v); also elsewhere on the board
W_DISABLE_1: PCB1.56 (W_DISABLE0#); also elsewhere on the board
W_DISABLE_2: PCB1.54 (W_DISABLE1#); also elsewhere on the board

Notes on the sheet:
M.2 edge connections

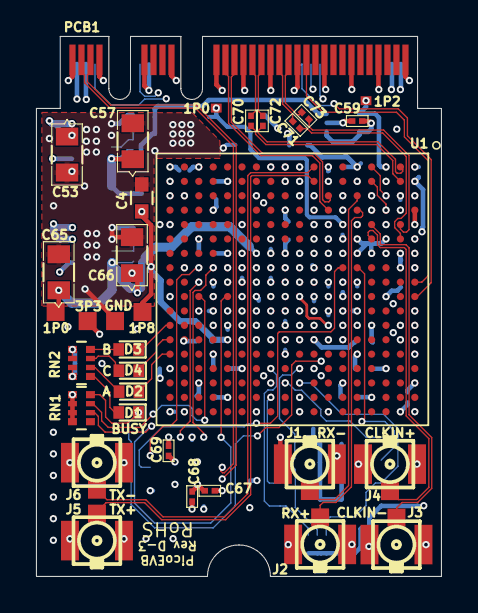
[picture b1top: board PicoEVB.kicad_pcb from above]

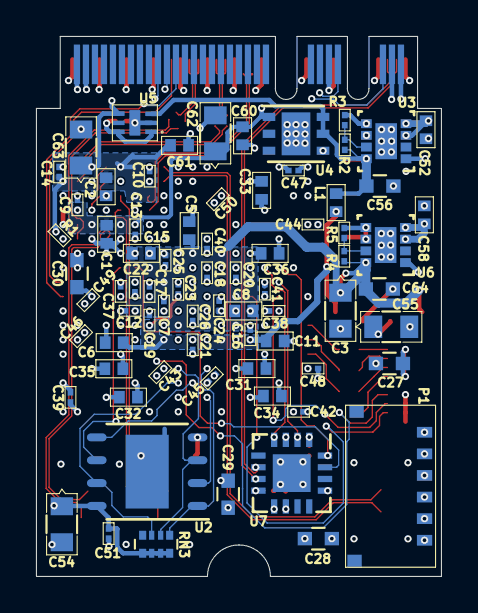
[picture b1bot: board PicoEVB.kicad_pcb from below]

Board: 4 copper layers, 22.5 x 30.0 mm, 107 parts (74 on the bottom side), 60 nets.

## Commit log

2017-05-17 Initial add
2017-05-18 Updating readme
2017-05-19 Fixed typos
2017-05-20 Added contact info
2017-06-09 Added GPLv2 licence to Xilinx driver code, per email from Xilinx Clarified compatible slots Added link to mPCIe->NGFF adapter
2017-06-21 Vivado project no longer stored as an archive, but rather in a format that is usable live
2017-07-01 Modified image per rev C copper Added PicoEVB images (will add to readme later)
2017-07-01 Added PicoEVB
2017-08-18 Adding link to Crowd Supply
2017-08-18 Added pre-built binaries suitable for downloading via cable Updated design to Gen 2
2017-08-18 Removing Vivado cache dir
2017-09-15 Updated schematic and block diagram to include latest rev
2017-09-21 Simplified FPGA design files Updated to Vivado 2017.2
2017-09-21 Move IP cache out of project folder (which gets regenerated every time project.tcl is sourced). Clean up some critical warnings for constraints that couldn't be applied correctly.
2017-09-23 Minor updates: - Updated mcs with output from actual build - Added upgrade info to readme - Fixed some constraints to remove warnings
2017-09-23 Xilinx example project up-to-date, now has performance tester
2017-09-23 Fixed typos in readme
2017-09-23 Updated readme, mostly editorial updates. Updated constraints - reorganized - added explicit constraints for pcie x1 link - added mgt loopback i/o constraints - added auxio constraints - removed fluf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
2017-10-17 Removing NanoEVB and updating PicoEVB to indicate it has I/O now
2017-10-28 Changed PCIe reset to have internal pulldown- needed for consistent link on some motherboards Fixed mcs generation command Added new MCS built using 2017.3 & latest IP
2017-10-28 Readme fixes
2017-10-28 Adding .hex file for external prom programming
2017-11-19 SPI flash now set to load @ 66MHz (+-50%). This increased the chances that the FPGA is configured in time to be recognized as a PCIe endpoint
2017-11-23 Added JTAG AXI master
2017-11-28 Cleaned up block diagram: - Removed unused JTAG AXI - Improved PCIe status LED - Other LEDs now under SW control
2017-12-06 Added hex files for FL132 part (Used on rev D) Added version number in first register
2018-01-11 Updating for Rev D
2018-01-13 Fixed compiler error - pci_enable_msix() is missing on newer kernels
2018-01-13 Adding helper script to build and install the driver for Linux. The driver will automatically loaded after the build, and reloaded on reboot
2018-01-15 Reorganizing to support more sample projects Added documentation for sample project 0 Added host code to sample project 0- demonstrates DMA transfer and blinking LEDs
2018-01-15 Attempting to fix botched tables
2018-01-15 Fixing more broken tables
2018-01-19 Moving Xilinx DMA driver to another location- its not really a part of this project Added licence files
2018-01-19 spelling
2018-01-19 More details in readme
2018-01-19 Added links to ebay and Amazon
2018-02-02 Removing ebay from links
2018-02-07 Using lower resolution image in main page to avoid slow page load
2018-02-14 Schematic PDF is now searchable
2018-03-06 Adding some images Adding links to product website
2018-03-06 Added images
2018-03-06 Fixed broken links to product website
2018-04-06 Added blurb for controlling LEDs for Windows users
2018-04-06 Fixed typo in comment
2018-05-21 Added M key adapter. Added EBay link
2018-11-11 Adding Kicad project; changed licence to GPLv3
2018-11-11 Added assorted scripts
2018-11-15 Simpifying project structure
2018-11-15 Adding MCS file back
2019-11-21 Updated for Vivado 2019. Now works with latest Vivado drivers. Added XADC and support for flash programming over PCIe
2019-11-21 Whoops adding correct MCS file which matches project
2019-11-21 Adding script to report FPGA temperature and voltage
2019-12-09 Fixed error- wrong MCS file name
2020-05-25 Adding initial flash loader project
2020-11-30 Added OpenOCD programming instructions
2021-11-13 Version 5: Built with Vivado 2021.1. Untested.
2025-12-04 Adding step file

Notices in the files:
parts and their libraries:
Copyright 2016 Accelerated Designs. All rights reserved.
